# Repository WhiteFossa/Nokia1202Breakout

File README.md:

# Nokia1202Breakout
Simple breakout board for Nokia 1202 LCD.

Done in KiCAD, uses my library - https://github.com/WhiteFossa/fossas_kicad_lib

GPLv3 licensed.

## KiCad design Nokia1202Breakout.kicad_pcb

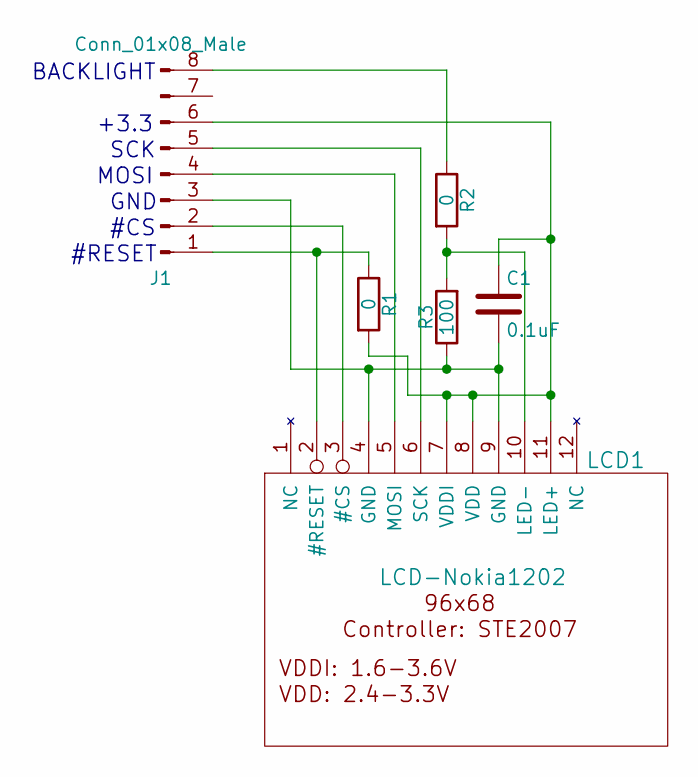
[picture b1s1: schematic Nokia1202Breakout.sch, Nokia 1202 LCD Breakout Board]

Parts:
C1: 0.1uF; C_0805
J1: Conn_01x08_Male; Pin_Header_Angled_1x08_Pitch2.54mm
LCD1: LCD-Nokia1202
R1, R2: 0; R_0805
R3: 100; R_0805

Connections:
unnamed: C1.1, J1.6, LCD1.7 (VDDI), LCD1.8 (VDD), LCD1.11 (LED+), R1.2
unnamed: C1.2, J1.3, LCD1.4 (GND), LCD1.9 (GND), R3.1
unnamed: J1.1, LCD1.2 (#RESET), R1.1
unnamed: J1.2, LCD1.3 (#CS)
unnamed: J1.4, LCD1.5 (MOSI)
unnamed: J1.5, LCD1.6 (SCK)
unnamed: J1.8, R2.1
unnamed: LCD1.10 (LED-), R2.2, R3.2

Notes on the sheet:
+3.3
#RESET
#CS
GND
MOSI
SCK
BACKLIGHT

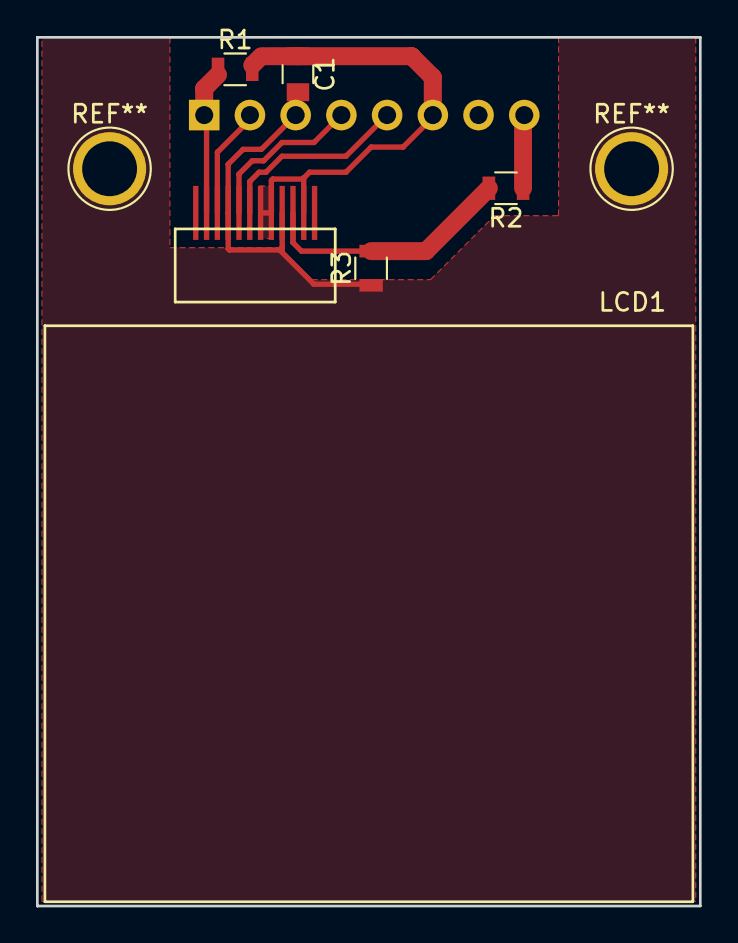
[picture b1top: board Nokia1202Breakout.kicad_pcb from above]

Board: 2 copper layers, 36.8 x 48.3 mm, 6 parts (1 on the bottom side), 8 nets.

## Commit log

2017-12-23 Updated readme.
2017-12-23 Looks like everything is ready.
2017-12-24 Fixed incorrect reset connection.
2017-12-24 Added mounting holes, prepared negative copies for photochemical printing.
